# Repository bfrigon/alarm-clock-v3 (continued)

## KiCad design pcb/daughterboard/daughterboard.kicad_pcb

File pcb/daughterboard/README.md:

### Bill of material ###

```
Date    : 2018-09-19
Doc. ID : CLKV3-SCH-06
Project : Alarm Clock (V3)
Title   : Daughterboard

Part #  : CLKV3-PC-06
REV.    : A

Components : 70
```

------------------------------------------------------------------------------------------------------------------------

| Qty | Ref.                     | Description                            | Value      | Part #                | Footprint                 |
|-----|--------------------------|----------------------------------------|------------|-----------------------|---------------------------|
| 1   | J7                       | Header - Single Row - 2 Pos            | ALARM SW   | DF3A-2P-2DSA          | conn-header:DF3A-2P-2DSA  |
| 1   | J1                       | Header - Single Row - 3 Pos            | LAMP       | DF3A-3P-2DSA          | conn-header:DF3A-3P-2DSA  |
| 1   | J3                       | Header - Single Row - 4 Pos            | SPKR       | DF3A-4P-2DSA          | conn-header:DF3A-4P-2DSA  |
| 1   | J2                       | Header - Single Row - 8 Pos            | DISPLAY    | DF3A-8P-2DSA          | conn-header:DF3A-8P-2DSA  |
| 1   | U2                       | Single inverter                        | -          | 74AHC1G04SE-7         | smt-sot:SOT-353           |
| 1   | U3                       | Dual 150mA LDO Regulator               | -          | AP7312-1833W6         | smt-sot:SOT23-6           |
| 1   | Q1                       | Single P-Channel MOSFET 20V 10A        | NTF6P02    | NTF6P02T3G            | smt-sot:SOT-223           |
| 1   | U5                       | Dual non-inverting buffer              | -          | SN74LVC2G34DBV        | smt-sot:SOT23-6           |
| 1   | U4                       | 2.8W/Ch Stereo Class-D Audio Amplifier | -          | TPA2016D2             | smt-qfn:QFN20-EP-4x4      |
| 1   | U1                       | MP3/AAC/MIDI Audio Codec               | -          | VS1053B               | smt-qfp:QFP-7-48          |
| 10  | R4, R6, R12-R19          | Resistor                               | 100k       | -                     | smt:R-0603                |
| 14  | C1-C10, C26-C27, C29-C30 | Capacitor                              | 100nF      | -                     | smt:C-0603                |
| 3   | R2, R7, R11              | Resistor                               | 10k        | -                     | smt:R-0603                |
| 2   | C18-C19                  | Capacitor                              | 10nF       | -                     | smt:C-0603                |
| 1   | R8                       | Resistor                               | 10         | -                     | smt:R-0603                |
| 3   | C11, C14, C16            | Electrolytic capacitor                 | 10uF 6V3   | -                     | smt:CPL-0805              |
| 3   | C24-C25, C28             | Capacitor                              | 10uF       | -                     | smt:C-0805                |
| 1   | R5                       | Resistor                               | 1M         | -                     | smt:R-0603                |
| 4   | C31-C34                  | Capacitor                              | 1nF        | -                     | smt:C-0603                |
| 5   | C15, C20-C23             | Capacitor                              | 1uF        | -                     | smt:C-0805                |
| 2   | C12-C13                  | Capacitor                              | 20pF       | -                     | smt:C-0603                |
| 2   | R9-R10                   | Resistor                               | 20         | -                     | smt:R-0603                |
| 2   | R1, R3                   | Resistor                               | 470        | -                     | smt:R-0603                |
| 1   | C17                      | Capacitor                              | 47nF       | -                     | smt:C-0603                |
| 2   | L1-L2                    | Ferrite                                | -          | 2508053007Y0          | smt:FER-0805              |
| 1   | Y1                       | Crystal                                | 12.288 MHz | ECS-122.8-20-3X-EN-TR | crystals:smt-CSM-3X-7x4mm |
| 4   | L3-L6                    | Ferrite                                | -          | MPZ1608S221A          | smt:FER-0603              |

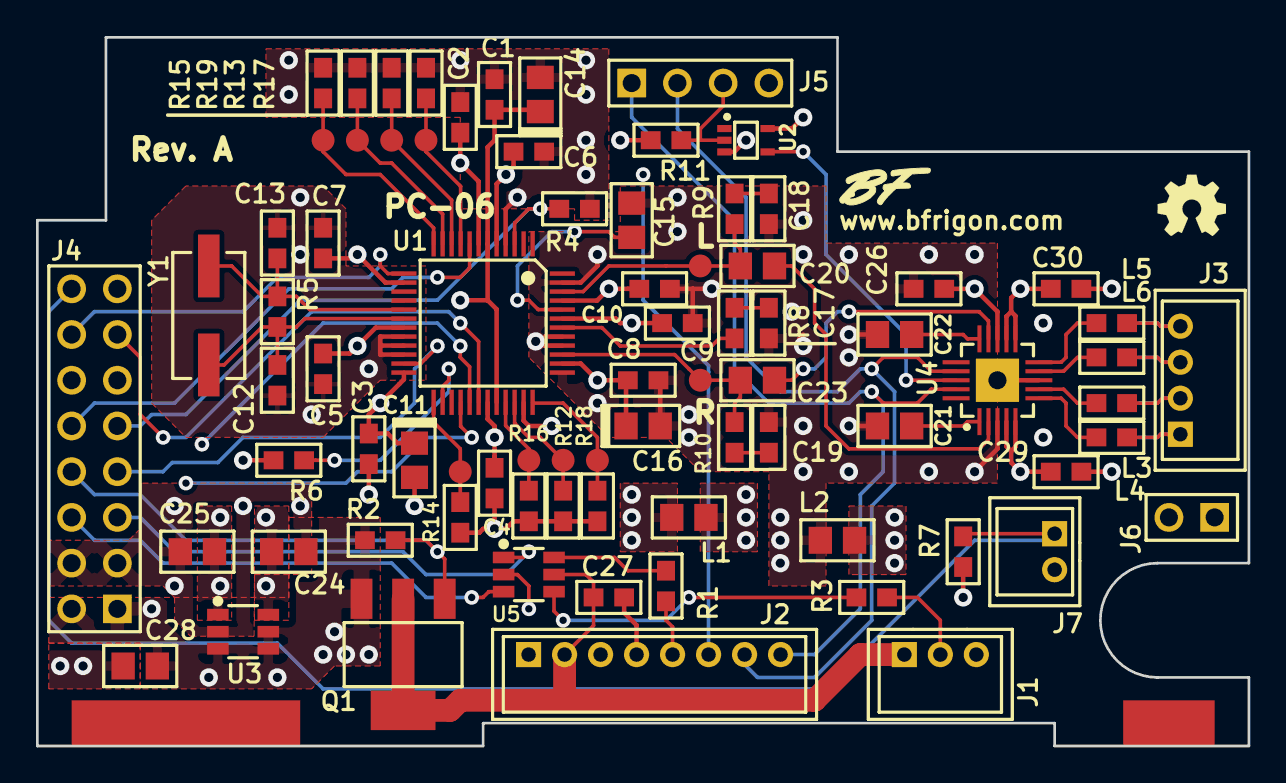
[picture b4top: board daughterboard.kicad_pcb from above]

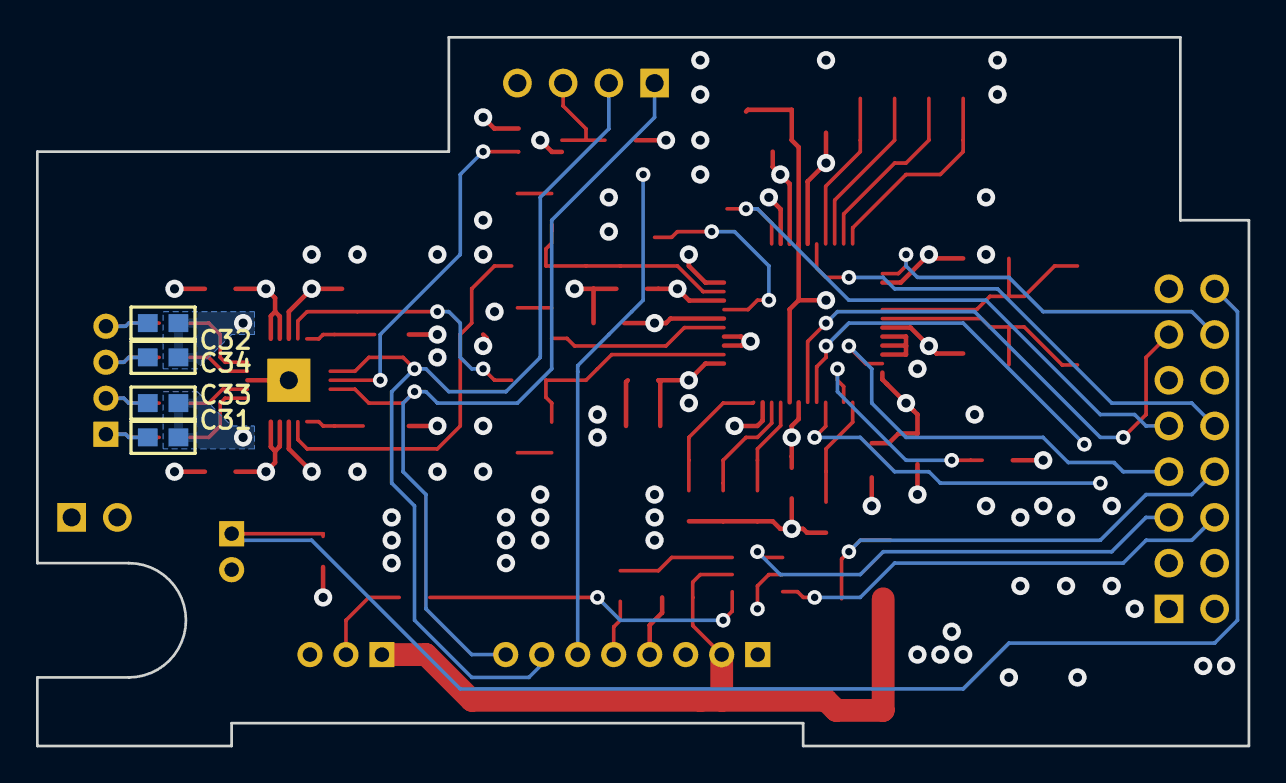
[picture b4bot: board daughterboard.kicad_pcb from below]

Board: 4 copper layers, 67.3 x 39.4 mm, 85 parts (4 on the bottom side), 57 nets.

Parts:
C1, C2, C3, C4, C5, C6, C7, C8, C9, C10, C26, C27, C29, C30: 100nF; C-0603
C11, C14, C16: 10uF 6V3; CPL-0805
C12, C13: 20pF; C-0603
C15, C20, C21, C22, C23: 1uF; C-0805
C17: 47nF; C-0603
C18, C19: 10nF; C-0603
C24, C25, C28: 10uF; C-0805
C31, C32, C33, C34: 1nF; C-0603
H1: Solder pad 2; SolderPad-100x500
H2: Solder Pad 2; SolderPad-100x200
J1: LAMP; DF3A-3P-2DSA
J2: DISPLAY; DF3A-8P-2DSA
J3: SPKR; DF3A-4P-2DSA
J4: DB-A; HDR-M-2x08
J5: DB-B; HDR-M-1x04
J6: DB-C; HDR-M-1x02
J7: ALARM SW; DF3A-2P-2DSA
L1, L2: 2508053007Y0; FER-0805
L3, L4, L5, L6: MPZ1608S221A; FER-0603
Q1: NTF6P02; SOT-223
R1, R3: 470; R-0603
R2, R7, R11: 10k; R-0603
R4, R6, R12, R13, R14, R15, R16, R17, R18, R19: 100k; R-0603
R5: 1M; R-0603
R8: 10; R-0603
R9, R10: 20; R-0603
TP1, TP2, TP3, TP4, TP5, TP6, TP7, TP8, TP9, TP10: TEST-POINT; TEST-POINT-50
U1: VS1053B; QFP-7-48
U2: 74AHC1G04SE-7; SOT-353
U3: AP7312-1833W6; SOT23-6
U4: TPA2016D2; QFN20-EP-4x4
U5: SN74LVC2G34DBV; SOT23-6
Y1: 12.288 MHz; smt-CSM-3X-7x4mm

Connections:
+1V8: C2.2, C3.2, C4.2, C6.2, C11.A, C24.2, U1.5, U1.7, U1.24, U1.31, U3.6
+3V3: C1.2, C5.2, C7.2, C14.A, C25.2, J4.15, L1.2, R6.1, U1.6, U1.14, U1.19, U1.32, U3.1
+5V: C28.2, C29.2, C30.2, J2.1, J4.1, J4.2, Q1.3, R2.2, R7.2, R11.2, U2.5, U3.3, U3.4, U3.5, U4.4, U4.5, U4.11, U4.12
/ALRM_SW: J4.16, J7.1, R7.1
/A_SHDN: J5.3, R11.1, U2.2
/CCS_3V3: J4.7, U1.23
/CMOSI_3V3: J4.11, U1.29
/CRST_3V3: J4.9, R4.1, U1.3
/DREQ: J4.10, U1.8
/GBUF: R8.2, U1.42
/GPIO0: R16.2, TP1.1, U1.33
/GPIO1: R12.2, TP2.1, U1.34
/GPIO2: R17.2, TP3.1, U1.9
/GPIO3: R13.2, TP4.1, U1.10
/GPIO4: R18.2, TP5.1, U1.36
/GPIO5: R14.2, TP6.1, U1.25
/GPIO6: R19.2, TP7.1, U1.11
/GPIO7: R15.2, TP8.1, U1.12
/KCHG: J2.6, J5.4
/LEFT: C20.2, R9.2, TP9.1, U1.46
/MISO: J4.13, U1.30
/OUT_L+: C33.1, J3.2, L3.2
/OUT_L-: C31.1, J3.1, L4.2
/OUT_R+: C34.2, J3.3, L6.2
/OUT_R-: C32.2, J3.4, L5.2
/PIX_CLK: J4.5, U5.1
/PIX_LAMP: J4.6, U5.3
/PIX_SHDN: J4.8, Q1.1, R2.1
/PIX_VCC: C27.2, J1.1, J2.2, Q1.2, Q1.4, U5.5
/RIGHT: C23.2, R10.2, TP10.1, U1.39
/SCL: J2.7, J5.2, U4.17
/SCLK_3V3: J4.12, U1.28
/SDA: J2.8, J5.1, U4.19
/XDCS_3V3: J4.14, U1.13
AGND: C8.1, C9.1, C10.1, C15.1, C16.K, C17.1, C18.1, C19.1, C21.2, C22.2, C26.1, C31.2, C32.1, C33.2, C34.1, L2.1, U1.37, U1.40, U1.41, U1.47, U4.3
AVDD: C8.2, C9.2, C10.2, C16.A, C26.2, L1.1, U1.38, U1.43, U1.45, U4.13
GND: C1.1, C2.1, C3.1, C4.1, C5.1, C6.1, C7.1, C11.K, C12.2, C13.2, C14.K, C24.1, C25.1, C27.1, C28.1, C29.1, C30.1, J1.3, J2.3, J2.4, J4.3, J4.4, J6.1, J6.2, J7.2, L2.2, R4.2, R12.1, R13.1, R14.1, R15.1, R16.1, R17.1, R18.1, R19.1, U1.4, U1.16, U1.20, U1.21, U1.22, U1.35, U2.3, U3.2, U4.8, U4.EP, U5.2
unnamed: C12.1, R5.2, U1.18, Y1.1
unnamed: C13.1, R5.1, U1.17, Y1.2
unnamed: C15.2, U1.44
unnamed: C17.2, R8.1
unnamed: C18.2, R9.1
unnamed: C19.2, R10.1
unnamed: C20.1, U4.2
unnamed: C21.1, U4.1
unnamed: C22.1, U4.15
unnamed: C23.1, U4.14
unnamed: J1.2, R3.2
unnamed: J2.5, R1.2
unnamed: L3.1, U4.7
unnamed: L4.1, U4.6
unnamed: L5.1, U4.10
unnamed: L6.1, U4.9
unnamed: R1.1, U5.6
unnamed: R3.1, U5.4
unnamed: R6.2, U1.26
unnamed: U2.4, U4.18

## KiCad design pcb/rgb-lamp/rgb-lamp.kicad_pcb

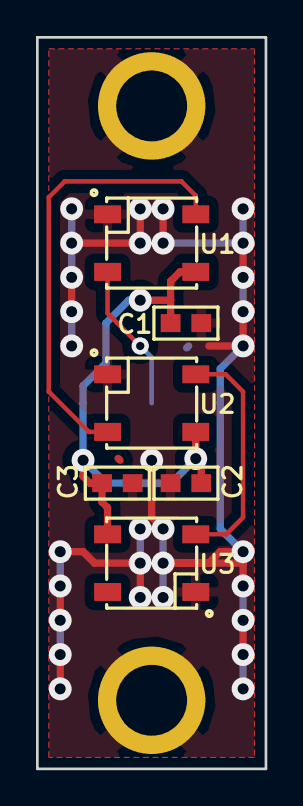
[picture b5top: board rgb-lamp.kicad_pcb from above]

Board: 2 copper layers, 12.7 x 40.6 mm, 9 parts (1 on the bottom side), 5 nets.

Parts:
C1, C2, C3: 100nF; C-0603
H1, H2: Hole; SM-Standoff-#2
J1: HEADER-1x03; WP-75mil-1x03
U1, U2, U3: IN-PI554FCH; LED-5050

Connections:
+5V: C1.1, C2.1, C3.1, J1.3, U1.1, U2.1, U3.1
GND: C1.2, C2.2, C3.2, H1.P, H2.P, J1.1, U1.3, U2.3, U3.3
unnamed: J1.2, U1.4
unnamed: U1.2, U2.4
unnamed: U2.2, U3.4

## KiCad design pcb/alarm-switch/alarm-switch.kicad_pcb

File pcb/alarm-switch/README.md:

### Bill of material ###

```
Date    : 2018-08-14
Doc. ID : CLKV3-SCH-09
Project : Alarm Clock V3
Title   : Alarm Switch Pcb

Part #  : CLKV3-PC-09
REV.    : A

Components : 1
```

------------------------------------------------------------------------------------------------------------------------

| Qty | Ref. | Description           | Value        | Part # | Footprint               |
|-----|------|-----------------------|--------------|--------|-------------------------|
| 1   | SW1  | Momentary SPST switch | L102011ML04Q | -      | switches:CK_L102XXXML04 |

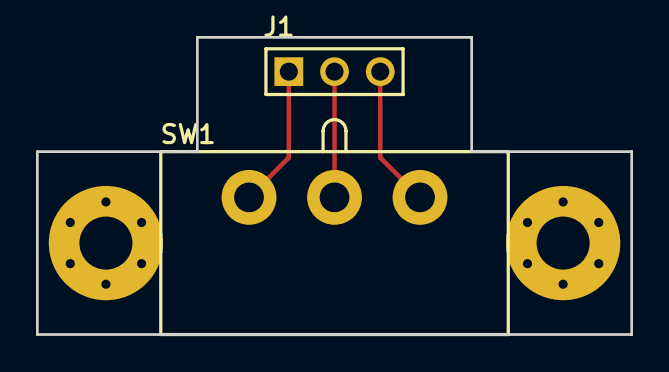
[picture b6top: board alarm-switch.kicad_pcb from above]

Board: 2 copper layers, 33.0 x 16.5 mm, 4 parts (0 on the bottom side), 4 nets.

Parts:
H1, H2: Hole; Hole-Screw-#4
J1: HEADER-1x03; HDR-M-1x03
SW1: L102011ML04Q; CK-L102XXXML04

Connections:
GND: H1.P, H2.P
unnamed: J1.1, SW1.1
unnamed: J1.2, SW1.2
unnamed: J1.3, SW1.3

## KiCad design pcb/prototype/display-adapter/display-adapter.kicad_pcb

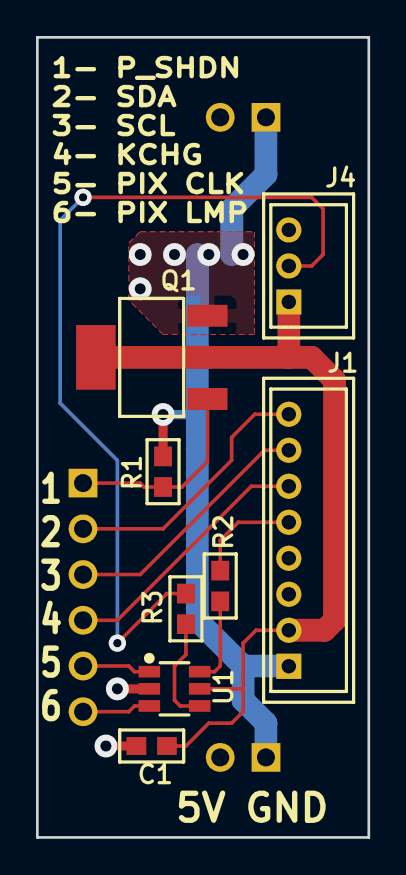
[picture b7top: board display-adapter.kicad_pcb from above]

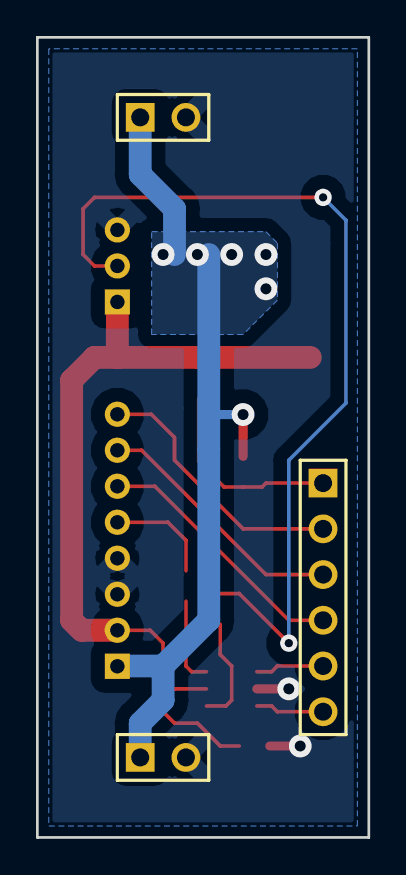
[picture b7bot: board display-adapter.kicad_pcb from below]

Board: 2 copper layers, 18.4 x 44.5 mm, 11 parts (3 on the bottom side), 13 nets.

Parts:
C1: 100nF; C-0603
J1: DISPLAY; DF3A-8P-2DSA
J2, J3: HEADER-1x02; HDR-M-1x02
J4: LAMP; DF3A-3P-2DSA
J5: HEADER-1x06; HDR-M-1x06
Q1: NTF6P02; SOT-223
R1: 10k; R-0603
R2, R3: 470; R-0603
U1: SN74LVC2G34DBV; SOT23-6

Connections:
+5V: J1.1, J2.1, J3.1, Q1.3, R1.2
/KCHG: J1.6, J5.4
/PIX_CLK: J5.5, U1.1
/PIX_LAMP: J5.6, U1.3
/PIX_SHDN: J5.1, Q1.1, R1.1
/PIX_VCC: C1.2, J1.2, J4.1, Q1.2, Q1.4, U1.5
/SCL: J1.7, J5.3
/SDA: J1.8, J5.2
GND: C1.1, J1.3, J1.4, J2.2, J3.2, J4.3, U1.2
unnamed: J1.5, R2.2
unnamed: J4.2, R3.2
unnamed: R2.1, U1.6
unnamed: R3.1, U1.4

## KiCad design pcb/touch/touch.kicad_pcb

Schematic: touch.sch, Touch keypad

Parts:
C1, C3: 1uF; C-0805
C2: 100nF; C-0603
C4: 3.3uF; C-0805
J1: HEADER-1x05; WP-50mil-1x05
Q1, Q2: BSS138; SOT23; Part BSS138
R1, R3, R7, R8: 10k; R-0603
R2: 100k; R-0603
R4, R5, R6: 470; R-0603
SW1: ALARM; TouchPad-700x600
SW2: MENU; TouchPad-700x600
SW3: SET; TouchPad-800x600
U1: AT42QT1070; SOIC14N
U2: LP2981-33DBVT; SOT23-5

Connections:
+3V3: C1.1, C2.1, C4.2, Q1.1, Q2.1, R2.1, R7.2, R8.2, U1.1, U2.5
+5V: C3.2, J1.5, R1.2, R3.2, U2.1, U2.3
/E_LEFT: R6.2, SW1.1
/E_RIGHT: R4.2, SW2.1
/E_SET: R5.2, SW3.1
/SCL_3V3: Q2.2, R8.1, U1.6
/SCL_5V: J1.2, Q2.3, R3.1
/SDA_3V3: Q1.2, R7.1, U1.3
/SDA_5V: J1.1, Q1.3, R1.1
/~CHANGE: J1.3, R2.2, U1.5
GND: C1.2, C2.2, C3.1, C4.1, J1.4, U1.2, U1.14, U2.2
unnamed: R4.1, U1.11
unnamed: R5.1, U1.10
unnamed: R6.1, U1.12

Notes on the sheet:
3.3V Regulator
I2C level shifter
I2C Addr. : 0x1B

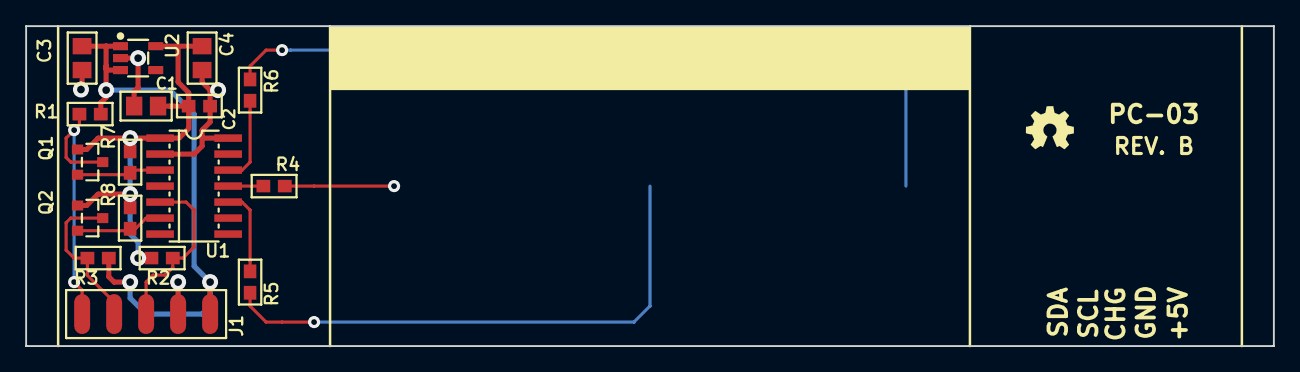
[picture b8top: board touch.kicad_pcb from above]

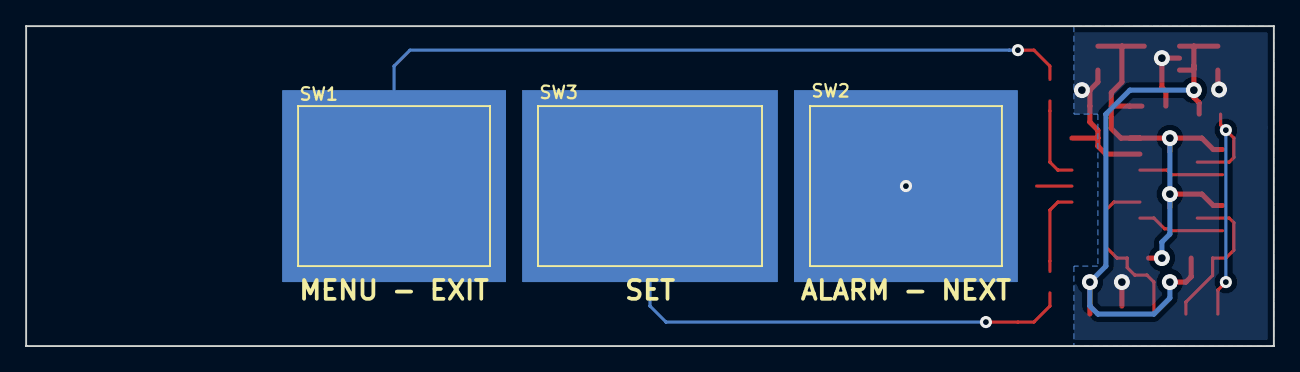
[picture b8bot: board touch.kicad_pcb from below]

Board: 2 copper layers, 99.1 x 25.4 mm, 20 parts (3 on the bottom side), 14 nets.

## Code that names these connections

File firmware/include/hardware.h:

//******************************************************************************
//
// Project : Alarm Clock V3
// File    : include/hardware.h
// Author  : Benoit Frigon <www.bfrigon.com>
//
// -----------------------------------------------------------------------------
//
// This work is licensed under the Creative Commons Attribution-ShareAlike 4.0
// International License. To view a copy of this license, visit
//
// http://creativecommons.org/licenses/by-sa/4.0/
//
// or send a letter to Creative Commons,
// PO Box 1866, Mountain View, CA 94042, USA.
//
//******************************************************************************

#ifndef HARDWARE_H
#define HARDWARE_H

#include <Arduino.h>
#include <SPI.h>
#include <Wire.h>
#include <avr/wdt.h>
#include <avr/pgmspace.h>
#include "drivers/tpa2016.h"
#include "drivers/vs1053.h"
#include "drivers/rtc.h"
#include "drivers/lamp.h"
#include "drivers/qt1070.h"
#include "drivers/us2066.h"
#include "drivers/neoclock.h"
#include "drivers/neopixel.h"
#include "drivers/wifi/wifi.h"
#include "drivers/bq27441.h"
#include "drivers/power.h"
#include "drivers/als.h"
#include "drivers/sdcard.h"



// ----------------------------------------
// Pins
// ----------------------------------------
#define PIN_INT_RTC         2
#define PIN_INT_KEYPAD      3
#define PIN_OLED_RESET      5
#define PIN_WIFI_CS         13
#define PIN_WIFI_IRQ        19
#define PIN_WIFI_RESET      11
#define PIN_WIFI_ENABLE     12
#define PIN_FACTORY_RESET   6
#define PIN_NEOCLOCK        37
#define PIN_PIX_LAMP        35
#define PIN_PIX_SHDN        30
#define PIN_ALARM_SW        25
#define PIN_VS1053_RESET    9
#define PIN_VS1053_DREQ     18
#define PIN_VS1053_CS       16
#define PIN_VS1053_SDCS     4
#define PIN_VS1053_XDCS     29
#define PIN_SD_DETECT       33
#define PIN_AMP_SHDN        28
#define PIN_ON_BATTERY      A14
#define PIN_SYSOFF          A8


// ----------------------------------------
// Devices I2C addresses
// ----------------------------------------
#define I2C_ADDR_OLED       0x3c
#define I2C_ADDR_TLS2561    0x29


#endif /* HARDWARE_H */

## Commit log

2016-05-26 Added mechanical drawings
2016-06-23 Updated mechanical drawings, display panel. Rev B
2016-06-23 Updated 3D model renders
2016-06-26 Updated drawings - Display panel
2016-06-26 Changed display panel STL object orientation
2016-07-03 Modified display panel frame, touch panel pcb
2016-07-05 Updated laser cut parts svg
2016-07-05 Updated mechanical drawings - Display panel Rev. B
2016-07-05 Changed symbolic links to hard links for schematics pdf
2016-07-11 * Fix wrong footprint for resistors (C-* to R-*) * Changed schematic sheet size to US letter
2016-07-11 Added gerber and pdf files of each layers for the touch PCB
2016-07-11 * Changed sheet size to US Letter * Added gerber and pdf files of each layers
2016-07-11 Remove mirror option for bottom layers
2016-07-11 Updated schematic of rgb-digits pcb * Changed sheet size to US letter * Added gerber and pdf files of each layers
2016-07-11 Added schematic for front panel pcb
2016-07-11 Updated speaker holder stl file
2016-07-11 Changed sheet size to US letter
2016-07-14 Added front panel pcb
2016-07-14 Modified daughterboard board layout
2016-07-14 Added pictures of display frame
2016-07-14 Moved 3d model renders to pictures directory
2016-07-15 Renamed picture directory
2016-07-15 Added light sensor pcb
2016-07-15 Added gerber files for light sensor pcb
2016-07-16 EN of 12V suply controlled from MCU instead of LCD GPIO
2016-07-16 Added No connect symbol for GPIO pin on LCD module
2016-07-17 Updated system overview diagram
2016-07-21 Removed 3.3v regulator and level shifters
2016-07-21 Changed touch keypad, front panel and light sensor pcb to a two layer design.
2016-07-21 Added panelized pcbs - display
2016-07-21 Updated system overview diagram to include the interrupt signal of the light sensor.
2016-07-22 Centered the light sensor horizontally
2016-07-22 Added pull down resistor to Reset line.
2016-07-22 Updated display pcb panel
2016-07-22 Deleted unneeded gerber files for layer 2 and 3 (gl2,gl3)
2018-08-22 Revised touch and front panel PCB, Added Motherboard PCB
2018-08-22 Initial firmware
2018-08-22 Modified directory structure, adjusted .gitignore
2018-08-24 Changed DC jack position on motherboard
2018-08-27 Updated fab files
2018-08-27 Changed print direction for back panel
2018-08-28 Adjusted page size for motherboard schematic
2018-08-28 Cleanup
2018-08-28 Added STL file for pcb assembly jig
2018-08-29 Replaced RGB leds with IN-PI554FCH instead of WS2812B
2018-09-19 Updated PCB design
    + Completed daughterboard PCB layout.
    * Corrected soldermask clerance on front panel pcb.
    - Removed input resistor on DIN for RGB lamp board.
    * Modified PCB layout for PSU board.
    * Updated gerber files.
    * Updated schematics pdf, BOM.
2018-09-19 Updated notes
2018-09-19 Added decals sheet
2018-09-20 Changed cap C13 from 100nF to 1uF
    * Use 1uF on C13 to generate a longer reset pulse when pressing the cfg/reset button.
2018-09-23 Replaced battery holder for Harwin S8411-45R
2018-09-24 Corrected bad description for part U9
2018-09-24 Fix: Wrong footprint for R20-22 and C14
2018-10-29 Corrected solder mask clearance
2018-10-29 Updated schematic pdf
2018-10-29 Updated panel gerber files
2018-10-29 Modified directory structure
2018-10-29 Added project pictures
2018-10-29 Corrected filename
2018-10-29 Renamed schematic files
2018-10-29 Updated enclosure base stl files
2018-11-06 Updated mechanical drawings
2018-11-09 Changed pin for VUSB detection on U3
2018-11-16 Switched to SdFat library, re-organized directory structure
2018-11-17 Code cleanup
2018-11-17 Implemented gradual alarm volume
2018-11-17 More code clean-up
2018-11-17 Changed directory structure
2018-11-18 Isolate read-only properties in Screen, ScreenItem
2018-11-18 Fix: Events callback set on wrong screen
2018-11-22 Implemented backup/restore config from SD card, other changes
    + Moved config related global function to new ConfigManager class
    + Added Backup/restore config to SD card functionality.
    + Reset to factory defaults from menu.
    + Power management : Added control pin SYSOFF
    + Base class for task management
    * Code cleanup
2018-11-22 Added runTask() to Alarm, Power and Neoclock
    * Checks for alarms, alarm sw changes inside Alarm::runtask()
    * Checks for keypad event and screen timeout inside Screen::runtask()
    * rtc : minute,hour,etc. values are accessible directly
    * FIX: If alarm switch state changes, only update screen in suspend mode
2018-11-25 Added battery holder model
2018-11-28 PSU board schematics/layout
2018-12-13 Added battery status screen
2018-12-13 Updated fisplay front cover design
2018-12-13 Changed VUSB-DET pin on USB-serial IC from 18 to 22
2018-12-31 Added final assembly pictures
2019-01-07 Bug fix: Read QT1070 interrupt pin level instead of relying on a flag
    Reads the interrupt pin level in the ProcessEvent routine to detect a
    key event instead of using an interrupt flag variable set in the ISR.
    This resolve occasional glitches where the keypad became unresponsive
    if the flag was cleared while an interrupt condition still existed.
    Since the QT1070 will hold the interrupt pin low as long as the data
    is not read, the interrupt is never raised again so the flag remains
2019-01-07 Battery gauge status: Display true battery capacity and SOC (unfiltered)
2020-08-24 Night lamp enable/disable available on all menus
    + Added driver for TSL2591
    * Fix Syntax for optional arguments
2020-08-24 Added fade out for the night lamp
2020-12-17 Added WiFi capability
    + Use TPA2016 AGC feature
    + Added network status screen
2020-12-21 Added serial console
    + Added ping capability to WiFi manager
    * Combined print functions common to console and LCD in the IPrint class
2020-12-23 Added net config console command
    * Allow to save/load clock and network configuration block independently
2020-12-29 Implemented time zones and daylight saving time
    - Removed swipe gestures as it cause key detection reliability issues
    * Hide input on console when entering WiFi password
2020-12-29 Added cache folder to .gitingore
2020-12-29 Modified .gitignore
2021-01-03 Added script to download and parse the IANA timezone database
    + Added printTimeInterval function to print interface
    * Store timezone in eeprom by name instead of the TZ table index
2021-01-05 Added command in console to set the time
2021-01-05 Removed kicad project files from .gitignore
2021-01-14 Add NTP client
2021-01-14 Added doxygen tags
2021-01-14 Added WINC1500C API library
2021-01-15 Fix tabulation in Doxygen tags
2021-01-15 Add console command alias to 'set date' and 'ping'
2021-01-15 Added console command for NTP client status
2021-01-17 Added history buffer for the console
2021-01-20 Added telnet console server
2021-01-20 Added option to disable telnet console
2021-01-21 Added a command to enable/disable services
2021-01-23 Load screen data from program memory
2021-01-24 Added printfln and printfln_P functions
2021-01-24 Removed 'this->' when accessing class variables
2021-01-31 Added menu for selecting the timezone
2021-01-31 Added time zone list in set timezone command
2021-02-01 Fix: Check screen list item out of range value
    Check for out of range value on item selection only if
    the item has a pointer to a variable.
2021-02-01 Sends multiple block of audio data to the codec
    Send up to 16 bocks of audio data to the codec per task run.
    This ensure that the audio buffering takes a higher
    priority over other tasks.
2021-02-03 Added display dimming relative to ambient lighting
2021-02-03 FIX: Keep auto-dimming from turning display off
2021-02-03 FIX: default ntp setting in 'set date' command
    'use ntp' default option not reflecting current value in config and
    always select no by default
2021-02-04 FIX: Use command history only on command prompts
2021-02-28 Moved project to PlatformIO
2021-03-15 Fix: Incorrect daylight saving transition rules
2021-07-12 Added battery status command to console
2023-01-08 Added event log feature
2023-01-24 Added MQTT/Home assistant support
    Publish alarm switch state changes, next alarm and
    WiFi RSSI to home assistant via a MQTT broker.
2023-01-25 Code clean-up
2023-01-29 Updated timezone data to 2022g
2023-01-30 Exposes battery status to Home Assistant
2023-01-31 Enable watchdog
2023-01-31 Fix: Mqtt auto-reconnect when connection lost
2023-02-05 Fix: Wait until WiFi is connected to sync clock
    * Don't attempt to auto-reconnect to MQTT broker
    while WiFi is busy processing another request.
    + Show ntp sync event in logs if +/- 10 seconds.
2023-02-06 Fix: MQTT 16-bit publish packet ID rollover to 1
2023-02-06 Fix: MQTT connect fail if WiFi is busy on boot
2023-02-06 Bump version to 2023.2.0
2023-02-06 Fix: First NTP sync at boot fail if WiFi is busy
2023-02-16 Added text sensor for displaying messages on the LCD from Home Assistant
2023-02-26 For Juliette...
2023-03-01 Updated SdFat to 2.2.0
2023-03-12 Added FTP server to access SD card files
2023-08-02 Removed duplicate device name from entities
2023-08-02 Updated tzdata to 2023c
